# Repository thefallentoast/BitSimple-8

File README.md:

# BitSimple-8
The BitSimple-8 is a W65C02S-based computer inspired on the Commander X16 (or X16) by Commander Computers, LLC.\
The name was suggested by @Toboter in the X16 discord so we went with it.

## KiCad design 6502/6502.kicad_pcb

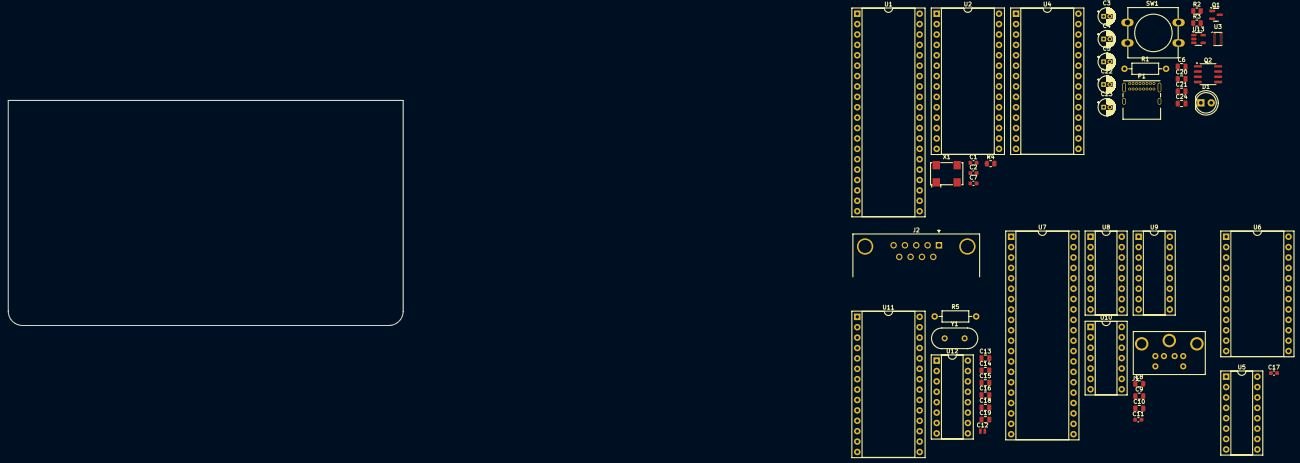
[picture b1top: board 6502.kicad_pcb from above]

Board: 2 copper layers, 96.5 x 55.0 mm, 51 parts (0 on the bottom side), 77 nets, no tracks yet.

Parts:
C1, C2, C17: 47nF; C_0603_1608Metric
C3, C4, C5, C22, C23: 10µF 25v; CP_Radial_D4.0mm_P1.50mm
C6, C24: 0.1uF 50V; C_0805_2012Metric
C7: 0.1µF; C_0603_1608Metric
C8, C19: 100nF; C_0805_2012Metric
C9, C10, C18: 47nF; C_0805_2012Metric
C11: 10nF; C_0603_1608Metric
C12: 30pF; C_0504_1310Metric
C13, C14, C15, C16: 1µF; C_0805_2012Metric
C20, C21: 1uF; C_0805_2012Metric
D1: RED; LED_D5.0mm
J1: Purple color - PS/2 keyboard; MINI-DIN-6-FULL-SHIELD
J2: DE9_Receptacle; DSUB-9_Female_Horizontal_P2.77x2.84mm_EdgePinOffset4.94mm_H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
P1: USB_C_Plug; USB_C_Receptacle_GCT_USB4085
Q1: AO3400A; SOT-23
Q2: AO4842; SOIC-8_3.9x4.9mm_P1.27mm
R1: 330Ω; R_Axial_DIN0207_L6.3mm_D2.5mm_P10.16mm_Horizontal
R2, R3: 10kΩ; R_0805_2012Metric
R4: 4.7kΩ; R_0805_2012Metric
R5: 1MΩ; R_Axial_DIN0207_L6.3mm_D2.5mm_P10.16mm_Horizontal
SW1: SW_Push; SW_PUSH-12mm
U1: W65C02SxP; DIP-40_W15.24mm_Socket
U2: CY62256-70PC; DIP-28_W15.24mm_Socket
U3: STM6600; TDFN-12_2x3mm_P0.5mm
U4: AT28C64B; DIP-28_W15.24mm_Socket
U5: 74HC137; DIP-16_W7.62mm_Socket
U6: 74LS154; DIP-24_W15.24mm_Socket
U7: W65C22SxP; DIP-40_W15.24mm_Socket
U8, U9: 74HC595; DIP-16_W7.62mm_Socket
U10: 74LS04; DIP-14_W7.62mm_Socket
U11: W65C51NxP; DIP-28_W15.24mm_Socket
U12: MAX232; DIP-16_W7.62mm_Socket
U13: AP2112K-1.2; SOT-23-5
X1: 5Mhz; Oscillator_SMD_IQD_IQXO70-4Pin_7.5x5.0mm
Y1: 1.8432Mhz; Crystal_HC49-U_Vertical

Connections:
+1V2: C21.1, C22.1, C23.1, C24.1, U13.5 (VOUT)
+5V: C1.1, C2.1, C3.1, C4.1, C5.1, C6.1, C7.1, C8.1, C9.1, C10.1, C11.1, C15.2, C17.1, C18.1, C19.1, C20.1, D1.2 (A), J1.4, P1.A4 (VBUS), P1.A9 (VBUS), P1.B4 (VBUS), P1.B9 (VBUS), R3.1, U1.8 (VDD), U2.28 (VCC), U3.1 (Vcc), U4.27 (~WE), U4.28 (VCC), U5.16 (VCC), U6.24 (VCC), U7.20 (VCC), U8.16 (VCC), U9.16 (VCC), U10.14 (VCC), U11.15 (VCC), U12.16 (VCC), U13.1 (VIN), U13.3 (EN), X1.4 (+Vs)
/CPU, Low ram and low rom/A0: U1.9 (A0), U2.10 (A0), U4.10 (A0)
/CPU, Low ram and low rom/A1: U1.10 (A1), U2.9 (A1), U4.9 (A1)
/CPU, Low ram and low rom/A2: U1.11 (A2), U2.8 (A2), U4.8 (A2)
/CPU, Low ram and low rom/A3: U1.12 (A3), U2.7 (A3), U4.7 (A3)
/CPU, Low ram and low rom/A4: U1.13 (A4), U2.6 (A4), U4.6 (A4)
/CPU, Low ram and low rom/A5: U1.14 (A5), U2.5 (A5), U4.5 (A5)
/CPU, Low ram and low rom/A6: U1.15 (A6), U2.4 (A6), U4.4 (A6)
/CPU, Low ram and low rom/A7: U1.16 (A7), U2.3 (A7), U4.3 (A7)
/CPU, Low ram and low rom/A8: U1.17 (A8), U2.25 (A8), U4.25 (A8)
/CPU, Low ram and low rom/A9: U1.18 (A9), U2.24 (A9), U4.24 (A9)
/CPU, Low ram and low rom/A10: U1.19 (A10), U2.21 (A10), U4.21 (A10)
/CPU, Low ram and low rom/A11: U1.20 (A11), U2.23 (A11), U4.23 (A11)
/CPU, Low ram and low rom/A12: U1.22 (A12), U2.2 (A12), U4.2 (A12)
/CPU, Low ram and low rom/A13: U1.23 (A13), U2.26 (A13)
/CPU, Low ram and low rom/A14: U1.24 (A14), U2.1 (A14)
/CPU, Low ram and low rom/D0: U1.33 (D0), U2.11 (Q0), U4.11 (I/O0)
/CPU, Low ram and low rom/D1: U1.32 (D1), U2.12 (Q1), U4.12 (I/O1)
/CPU, Low ram and low rom/D2: U1.31 (D2), U2.13 (Q2), U4.14 (I/O2)
/CPU, Low ram and low rom/D3: U1.30 (D3), U2.15 (Q3), U4.15 (I/O3)
/CPU, Low ram and low rom/D4: U1.29 (D4), U2.16 (Q4), U4.16 (I/O4)
/CPU, Low ram and low rom/D5: U1.28 (D5), U2.17 (Q5), U4.17 (I/O5)
/CPU, Low ram and low rom/D6: U1.27 (D6), U2.18 (Q6), U4.18 (I/O6)
/CPU, Low ram and low rom/D7: U1.26 (D7), U2.19 (Q7), U4.19 (I/O7)
/CPU, Low ram and low rom/PHI0: R4.1, U1.37 (ϕ0), X1.3 (Output)
/CPU, Low ram and low rom/PHI2: U1.39 (ϕ2), U7.25 (ϕ2), U11.27 (ϕ2)
/CPU, Low ram and low rom/R/~W: U1.34 (R/~W), U7.22 (R/~W), U11.28 (R/~W)
/CPU, Low ram and low rom/~DMA: U1.36 (BE), X1.1 (EN)
/CPU, Low ram and low rom/~IRQ: U1.4 (~IRQ), U7.21 (~IRQ), U11.26 (~IRQ)
/CPU, Low ram and low rom/~LROMS: U4.20 (~CE), U5.9 (~Y6)
/CPU, Low ram and low rom/~RES: U1.40 (~RES), U7.34 (~RES), U11.4 (~RES)
/Decoding & Logic/A15: U2.20 (~CS), U5.3 (A2), U5.6 (E2)
/expansion/KBD VIA ~EN: U6.1 (S0), U7.23 (~CS2)
/expansion/Keyboard VIA/PA0: U7.2 (PA0), U8.15 (QA)
/expansion/Keyboard VIA/PA1: U7.3 (PA1), U8.1 (QB)
/expansion/Keyboard VIA/PA2: U7.4 (PA2), U8.2 (QC)
/expansion/Keyboard VIA/PA3: U7.5 (PA3), U8.3 (QD)
/expansion/Keyboard VIA/PA4: U7.6 (PA4), U8.4 (QE)
/expansion/Keyboard VIA/PA5: U7.7 (PA5), U8.5 (QF)
/expansion/Keyboard VIA/PA6: U7.8 (PA6), U8.6 (QG)
/expansion/Keyboard VIA/PA7: U7.9 (PA7), U8.7 (QH)
/expansion/Keyboard VIA/PB5: U7.15 (PB5), U9.5 (QF)
/expansion/Keyboard VIA/PB6: U7.16 (PB6), U9.6 (QG)
/expansion/Keyboard VIA/PB7: U7.17 (PB7), U9.7 (QH)
/expansion/Keyboard VIA/PS2_D: J1.1, U8.14 (SER)
/expansion/Keyboard VIA/RCLK: U8.12 (RCLK), U9.12 (RCLK), U10.4
/expansion/Keyboard VIA/SRCLK: U8.11 (SRCLK), U9.11 (SRCLK), U10.1, U10.6
/expansion/UART 1 ~EN: U6.2 (S1), U11.3 (~CS2)
/expansion/~IOEN: U5.11 (~Y4), U6.18 (E0)
GND: C1.2, C2.2, C3.2, C4.2, C5.2, C6.2, C7.2, C8.2, C9.2, C10.2, C11.2, C12.2, C16.2, C17.2, C18.2, C19.2, C20.2, C21.2, C22.2, C23.2, C24.2, J1.3, J1.7, J2.5, P1.A1 (GND), P1.A12 (GND), P1.B1 (GND), P1.B12 (GND), P1.S1 (SHIELD), Q1.1 (G), Q2.1 (S1), Q2.7 (D1), Q2.8 (D1), R1.2, R4.2, SW1.1, U1.21 (VSS), U2.14 (GND), U3.12 (GND), U5.4 (~LE), U5.5 (~E1), U5.8 (GND), U6.12 (GND), U7.1 (VSS), U8.8 (GND), U8.13 (~OE), U9.8 (GND), U9.13 (~OE), U10.7 (GND), U11.1 (VSS), U12.15 (GND), U13.2 (GND), X1.2 (GND)
unnamed: D1.1 (K), R1.1
unnamed: J1.5, U10.5
unnamed: Q1.3 (D), R3.2
unnamed: Q1.2 (S), U3.4 (PS_HOLD)
unnamed: Q2.2 (G1), R2.1
unnamed: R2.2, U3.9 (~EN/EN)
unnamed: SW1.2, U3.6 (~PB)
unnamed: U8.9 (QH'), U9.14 (SER)
unnamed: U10.2, U10.3
unnamed: U11.12 (RxD), U12.12 (R1OUT)
unnamed: U11.10 (TxD), U12.11 (T1IN)
unnamed: C12.1, R5.1, U11.6 (XTAL1), Y1.2
unnamed: R5.2, U11.7 (XTAL2), Y1.1
unnamed: J2.8, U11.9 (~CTS)
unnamed: J2.1, U11.16 (~DCD)
unnamed: J2.6, U11.17 (~DSR)
unnamed: J2.4, U11.11 (~DTR)
unnamed: J2.7, U11.8 (~RTS)
unnamed: C13.1, U12.1 (C1+)
unnamed: C13.2, U12.3 (C1-)
unnamed: C14.1, U12.4 (C2+)
unnamed: C14.2, U12.5 (C2-)
unnamed: J2.2, U12.8 (R2IN)
unnamed: J2.3, U12.14 (T1OUT)
unnamed: C15.1, U12.2 (VS+)
unnamed: C16.1, U12.6 (VS-)

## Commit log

2024-08-05 Added the KiCAD project files
    Added the KiCAD project files as of revision 0.dev.14.
    PCB will be done on version 1.dev
2024-08-05 Update README.md
    Smol update :3
2024-08-05 Update README.md
    another smol update :3
